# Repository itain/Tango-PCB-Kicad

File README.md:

Use Kicad to remodel LinuxCNC-Rio Tangoboard.

This project created on Fedora 38 using Kicad-7.0.9.

Work in progress.

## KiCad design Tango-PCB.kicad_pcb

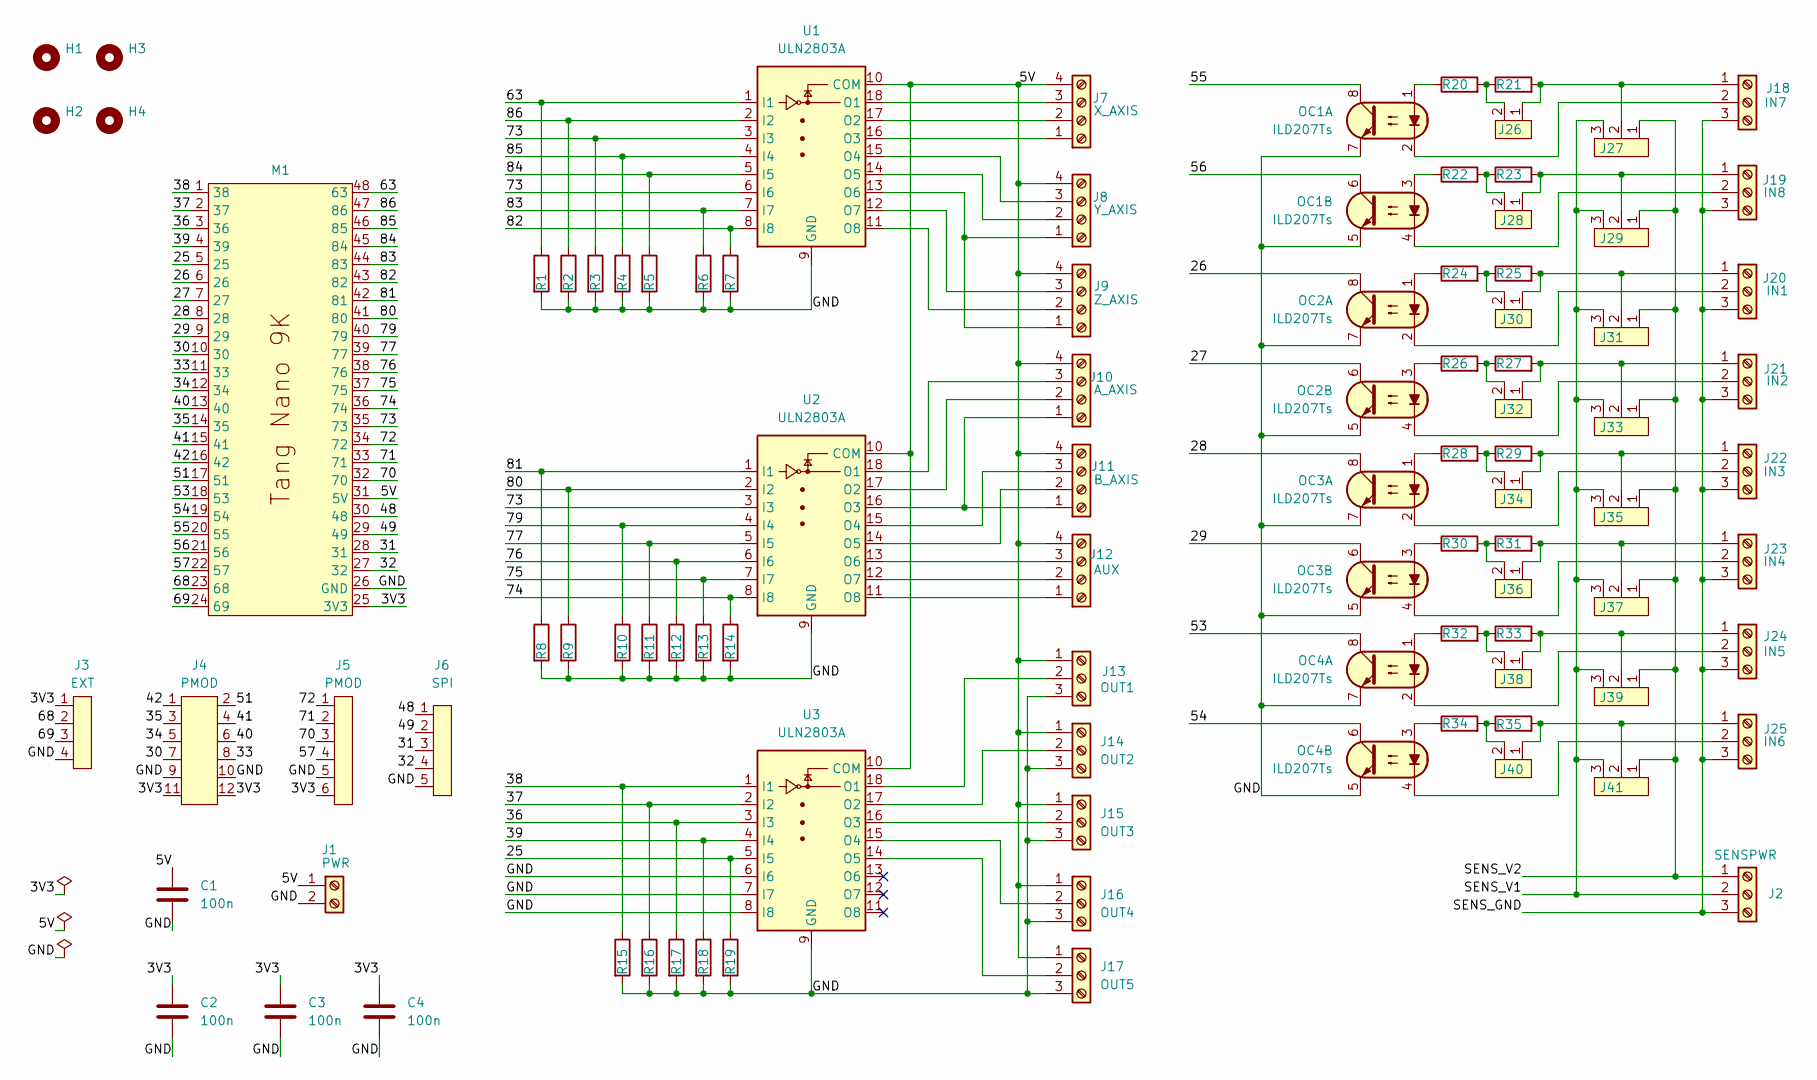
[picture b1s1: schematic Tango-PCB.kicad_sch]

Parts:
C1, C2, C3, C4: 100n; C_0805_2012Metric
H1, H2, H3, H4: MountingHole; MountingHole_3.2mm_M3_Pad
J1: PWR; TerminalBlock_Phoenix_PT-1,5-2-3.5-H_1x02_P3.50mm_Horizontal
J2: SENSPWR; TerminalBlock_Phoenix_PT-1,5-3-3.5-H_1x03_P3.50mm_Horizontal
J3: EXT; PinHeader_1x04_P2.54mm_Vertical
J4: PMOD; Conn_02X06_PinHeader
J5: PMOD; PinHeader_1x06_P2.54mm_Vertical
J6: SPI; JST_XH_S5B-XH-A_1x05_P2.50mm_Horizontal
J7: X_AXIS; TerminalBlock_Phoenix_PT-1,5-4-3.5-H_1x04_P3.50mm_Horizontal
J8: Y_AXIS; TerminalBlock_Phoenix_PT-1,5-4-3.5-H_1x04_P3.50mm_Horizontal
J9: Z_AXIS; TerminalBlock_Phoenix_PT-1,5-4-3.5-H_1x04_P3.50mm_Horizontal
J10: A_AXIS; TerminalBlock_Phoenix_PT-1,5-4-3.5-H_1x04_P3.50mm_Horizontal
J11: B_AXIS; TerminalBlock_Phoenix_PT-1,5-4-3.5-H_1x04_P3.50mm_Horizontal
J12: AUX; TerminalBlock_Phoenix_PT-1,5-4-3.5-H_1x04_P3.50mm_Horizontal
J13: OUT1; TerminalBlock_Phoenix_PT-1,5-3-3.5-H_1x03_P3.50mm_Horizontal
J14: OUT2; TerminalBlock_Phoenix_PT-1,5-3-3.5-H_1x03_P3.50mm_Horizontal
J15: OUT3; TerminalBlock_Phoenix_PT-1,5-3-3.5-H_1x03_P3.50mm_Horizontal
J16: OUT4; TerminalBlock_Phoenix_PT-1,5-3-3.5-H_1x03_P3.50mm_Horizontal
J17: OUT5; TerminalBlock_Phoenix_PT-1,5-3-3.5-H_1x03_P3.50mm_Horizontal
J18: IN7; TerminalBlock_Phoenix_PT-1,5-3-3.5-H_1x03_P3.50mm_Horizontal
J19: IN8; TerminalBlock_Phoenix_PT-1,5-3-3.5-H_1x03_P3.50mm_Horizontal
J20: IN1; TerminalBlock_Phoenix_PT-1,5-3-3.5-H_1x03_P3.50mm_Horizontal
J21: IN2; TerminalBlock_Phoenix_PT-1,5-3-3.5-H_1x03_P3.50mm_Horizontal
J22: IN3; TerminalBlock_Phoenix_PT-1,5-3-3.5-H_1x03_P3.50mm_Horizontal
J23: IN4; TerminalBlock_Phoenix_PT-1,5-3-3.5-H_1x03_P3.50mm_Horizontal
J24: IN5; TerminalBlock_Phoenix_PT-1,5-3-3.5-H_1x03_P3.50mm_Horizontal
J25: IN6; TerminalBlock_Phoenix_PT-1,5-3-3.5-H_1x03_P3.50mm_Horizontal
J26, J28, J30, J32, J34, J36, J38, J40: Led resistor select; PinHeader_1x02_P2.54mm_Vertical
J27, J29, J31, J33, J35, J37, J39, J41: Sense Power Select; PinHeader_1x03_P2.54mm_Vertical
M1: TangNano9k
OC1, OC2, OC3, OC4: ILD207Ts; SOIC-8_3.9x4.9mm_P1.27mm
R1, R2, R3, R4, R5, R6, R7, R8, R9, R10, R11, R12, R13, R14, R15, R16, R17, R18, R19, R20, R21, R22, R23, R24, R25, R26, R27, R28, R29, R30, R31, R32, R33, R34, R35: R; R_0805_2012Metric
U1, U2, U3: ULN2803A; SOIC-18W_7.5x11.6mm_P1.27mm

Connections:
/3V3: C2.1, C3.1, C4.1, J3.1, J4.11, J4.12, J5.6, M1.25 (3V3)
/5V: C1.1, J1.1, J7.4, J8.4, J9.4, J10.4, J11.4, J12.4, J13.1, J14.1, J15.1, J16.1, J17.1, M1.31 (5V), U1.10 (COM), U2.10 (COM), U3.10 (COM)
/25: M1.5 (25), R19.1, U3.5 (I5)
/26: M1.6 (26), OC2.8
/27: M1.7 (27), OC2.6
/28: M1.8 (28), OC3.8
/29: M1.9 (29), OC3.6
/30: J4.7, M1.10 (30)
/31: J6.3, M1.28 (31)
/32: J6.4, M1.27 (32)
/33: J4.8, M1.11 (33)
/34: J4.5, M1.12 (34)
/35: J4.3, M1.14 (35)
/36: M1.3 (36), R17.1, U3.3 (I3)
/37: M1.2 (37), R16.1, U3.2 (I2)
/38: M1.1 (38), R15.1, U3.1 (I1)
/39: M1.4 (39), R18.1, U3.4 (I4)
/40: J4.6, M1.13 (40)
/41: J4.4, M1.15 (41)
/42: J4.1, M1.16 (42)
/48: J6.1, M1.30 (48)
/49: J6.2, M1.29 (49)
/51: J4.2, M1.17 (51)
/53: M1.18 (53), OC4.8
/54: M1.19 (54), OC4.6
/55: M1.20 (55), OC1.8
/56: M1.21 (56), OC1.6
/57: J5.4, M1.22 (57)
/63: M1.48 (63), R1.1, U1.1 (I1)
/68: J3.2, M1.23 (68)
/69: J3.3, M1.24 (69)
/70: J5.3, M1.32 (70)
/71: J5.2, M1.33 (71)
/72: J5.1, M1.34 (72)
/73: M1.35 (73), R3.1, U1.3 (I3), U1.6 (I6), U2.3 (I3)
/74: M1.36 (74), R14.1, U2.8 (I8)
/75: M1.37 (75), R13.1, U2.7 (I7)
/76: M1.38 (76), R12.1, U2.6 (I6)
/77: M1.39 (77), R11.1, U2.5 (I5)
/79: M1.40 (79), R10.1, U2.4 (I4)
/80: M1.41 (80), R9.1, U2.2 (I2)
/81: M1.42 (81), R8.1, U2.1 (I1)
/82: M1.43 (82), R7.1, U1.8 (I8)
/83: M1.44 (83), R6.1, U1.7 (I7)
/84: M1.45 (84), R5.1, U1.5 (I5)
/85: M1.46 (85), R4.1, U1.4 (I4)
/86: M1.47 (86), R2.1, U1.2 (I2)
/GND: C1.2, C2.2, C3.2, C4.2, J1.2, J3.4, J4.9, J4.10, J5.5, J6.5, J13.3, J14.3, J15.3, J16.3, J17.3, M1.26 (GND), OC1.5, OC1.7, OC2.5, OC2.7, OC3.5, OC3.7, OC4.5, OC4.7, R1.2, R2.2, R3.2, R4.2, R5.2, R6.2, R7.2, R8.2, R9.2, R10.2, R11.2, R12.2, R13.2, R14.2, R15.2, R16.2, R17.2, R18.2, R19.2, U1.9 (GND), U2.9 (GND), U3.6 (I6), U3.7 (I7), U3.8 (I8), U3.9 (GND)
/SENS_GND: J2.3, J18.3, J19.3, J20.3, J21.3, J22.3, J23.3, J24.3, J25.3
/SENS_V1: J2.2, J27.3, J29.3, J31.3, J33.3, J35.3, J37.3, J39.3, J41.3
/SENS_V2: J2.1, J27.1, J29.1, J31.1, J33.1, J35.1, J37.1, J39.1, J41.1
unnamed: J7.1, U1.16 (O3)
unnamed: J7.2, U1.17 (O2)
unnamed: J7.3, U1.18 (O1)
unnamed: J8.1, J9.1, U1.13 (O6)
unnamed: J8.2, U1.14 (O5)
unnamed: J8.3, U1.15 (O4)
unnamed: J9.2, U1.11 (O8)
unnamed: J9.3, U1.12 (O7)
unnamed: J10.1, J11.1, U2.16 (O3)
unnamed: J10.2, U2.17 (O2)
unnamed: J10.3, U2.18 (O1)
unnamed: J11.2, U2.14 (O5)
unnamed: J11.3, U2.15 (O4)
unnamed: J12.1, U2.11 (O8)
unnamed: J12.2, U2.12 (O7)
unnamed: J12.3, U2.13 (O6)
unnamed: J13.2, U3.18 (O1)
unnamed: J14.2, U3.17 (O2)
unnamed: J15.2, U3.16 (O3)
unnamed: J16.2, U3.15 (O4)
unnamed: J17.2, U3.14 (O5)
unnamed: J18.1, J26.1, J27.2, R21.2
unnamed: J18.2, OC1.2
unnamed: J19.1, J28.1, J29.2, R23.2
unnamed: J19.2, OC1.4
unnamed: J20.1, J30.1, J31.2, R25.2
unnamed: J20.2, OC2.2
unnamed: J21.1, J32.1, J33.2, R27.2
unnamed: J21.2, OC2.4
unnamed: J22.1, J34.1, J35.2, R29.2
unnamed: J22.2, OC3.2
unnamed: J23.1, J36.1, J37.2, R31.2
unnamed: J23.2, OC3.4
unnamed: J24.1, J38.1, J39.2, R33.2
unnamed: J24.2, OC4.2
unnamed: J25.1, J40.1, J41.2, R35.2
unnamed: J25.2, OC4.4
unnamed: J26.2, R20.2, R21.1
unnamed: J28.2, R22.2, R23.1
unnamed: J30.2, R24.2, R25.1
unnamed: J32.2, R26.2, R27.1
unnamed: J34.2, R28.2, R29.1
unnamed: J36.2, R30.2, R31.1
unnamed: J38.2, R32.2, R33.1
unnamed: J40.2, R34.2, R35.1
unnamed: OC1.1, R20.1
unnamed: OC1.3, R22.1
unnamed: OC2.1, R24.1
unnamed: OC2.3, R26.1
unnamed: OC3.1, R28.1
unnamed: OC3.3, R30.1
unnamed: OC4.1, R32.1
unnamed: OC4.3, R34.1

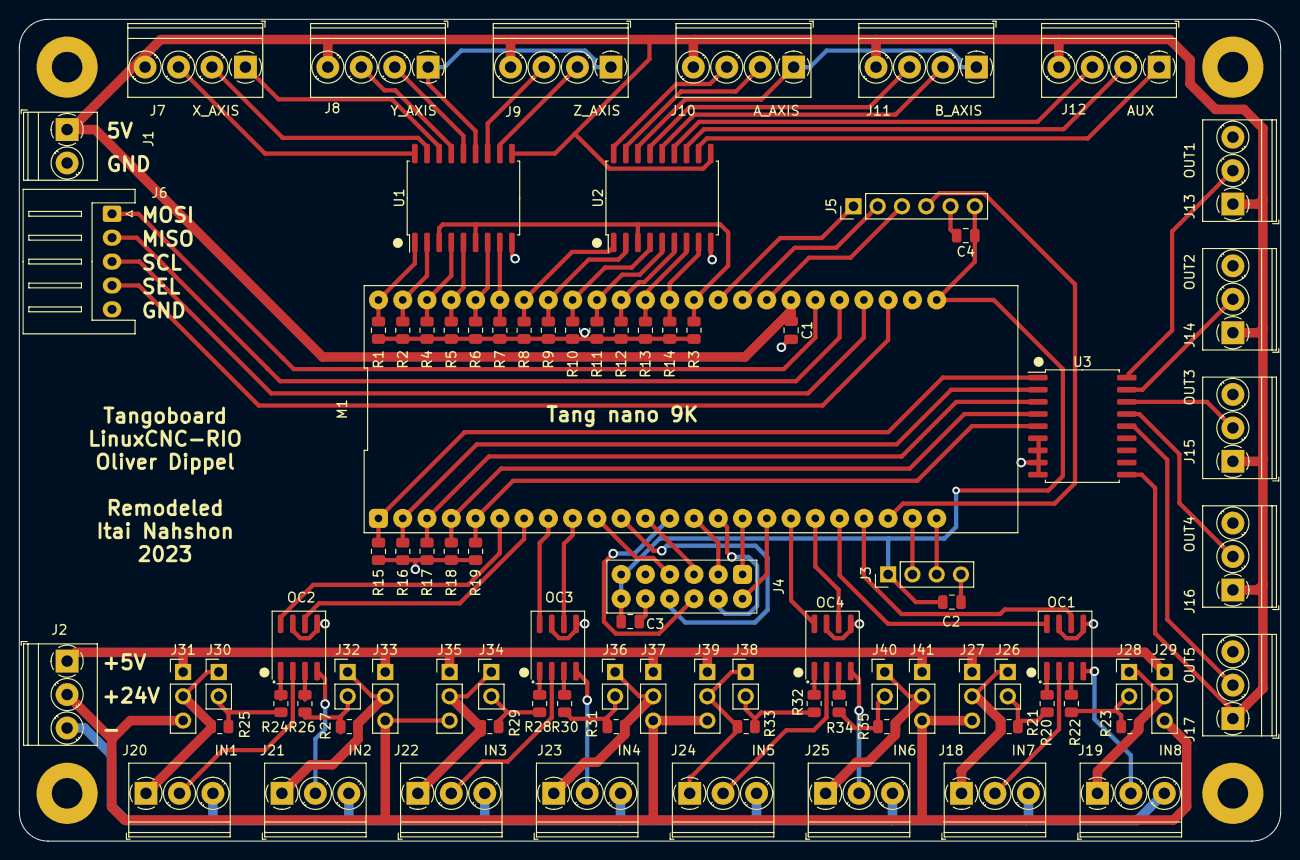
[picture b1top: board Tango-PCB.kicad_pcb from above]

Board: 2 copper layers, 132.0 x 86.0 mm, 92 parts (0 on the bottom side), 104 nets.

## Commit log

2023-11-17 Add SPI connector
2023-12-02 V2 - Individually select inputs 5V or 24V. Select input resistor.
2023-12-23 Updates.
2023-12-23 Update.
